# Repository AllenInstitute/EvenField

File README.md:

# EvenField - An easy, cost effective alternative to commercial based illumination systems for fluorescence microscopy

Coherent laser sources with Gaussian output profiles have been a preferred choice in many optical microscopy systems due to their high spatial intensity and monochromaticity. While these traits can beneficial in many applications, the high spatial coherence of these lasers results in interference effects as the light propagates through various optics toward the sample plane. These inference patterns superimposed onto the Gaussian laser profile result in an uneven illumination of the sample that get transferred into resulting images. For applications such as single molecule fluorescence imaging, the resulting field inhomogeneity  often clouds the signal that is to be detected. In addition, when these sources are used for imaging large areas that require tiling of multiple fields of view, the circular 2D illumination profile excites a larger field of view than is captured by the camera resulting in additional, unneeded photobleaching of these areas.

A simple deployment of a square multimode fiber between the illumination source and destination corrects this issue; however, the propogation of multiple laser modes through the fiber increases the potential for interference and results in additional laser speckle noise in the output beam. Researchers have developed several solutions to circumvent the laser speckle problem including, fiber vibration, tunable oscillating lenses, and spinning diffusers. 

We test some of these solutions and compare them to a commercial product, the Borealis system by Andor. 

----

Our full evaluation of this system can be found in our preprint : 
https://www.biorxiv.org/content/10.1101/2021.04.20.440683v1
  
---
  
We converged on a simple, cost-effective solution which we call the EvenField Illumination system. 

## So you're interested in building the EvenField system? ...We've got you covered.

This repository contains all of the information you will need to get started on building and employing the Evenfield system in your lab. This system can be used on a traditional, commercial laser launch or can be combined with the open source [Nicolase 3500] diode combiner and fiber launch for a cost effective, total solution for your illumination needs.

#### Hardware:
A complete list of associated hardware can be found [here](/Hardware).

This folder contains everything needed to build the EvenField system, including: 

* A complete [bill of materials] (optics and mounts)
* CAD renderings and .STEP files for the spinning diffuser component
* Details on custom optical fiber from Mitsubishi Cable Industries (MCI).
* Illuminator module for easy sensor size matching
* *Coming Soon:* Optical alignment guide 

#### Analysis:
The analysis code used for the EvenField publication has also been provided within this repo and may prove useful for evaluating the field flatness of your system. Code was written in Python and can be found [here].

[Nicolase 3500]: https://github.com/PRNicovich/NicoLase 
[bill of materials]: https://github.com/AllenInstitute/EvenField/blob/master/Hardware/EvenField%20Parts%20List.md
[here]: https://github.com/AllenInstitute/EvenField/tree/master/Analysis

#### Zoom illuminator update
Building on the published EvenField coupler and illuminator design, we implemented a microscope illuminator that features straightforward alignment and sensor-shape matching.  Illumination energy is delivered through an optical fiber - the details of which are not critical for use - and into a homogenizing prism.  The square exit face of this prism is imaged by a commercially-available zoom camera lens and a tube + objective lens pair to the sample plane.  Adjustments to the size and focus of the illumination field are straightfoward using the zoom and focus rings on the camera lens. On its own this assembly provides a simple and cheap square-field illumninator that will work with a wide range of detection camera formats.  Together with the EvenField homogenizer and NicoLase laser launch you can build your own microscopy illumination platform with custom laser power, color, and timing, evenly distributed over a field matching the detection camera FOV.  Add a chassis, cube, objective, and camera, and you've got a fluorescence microscope.

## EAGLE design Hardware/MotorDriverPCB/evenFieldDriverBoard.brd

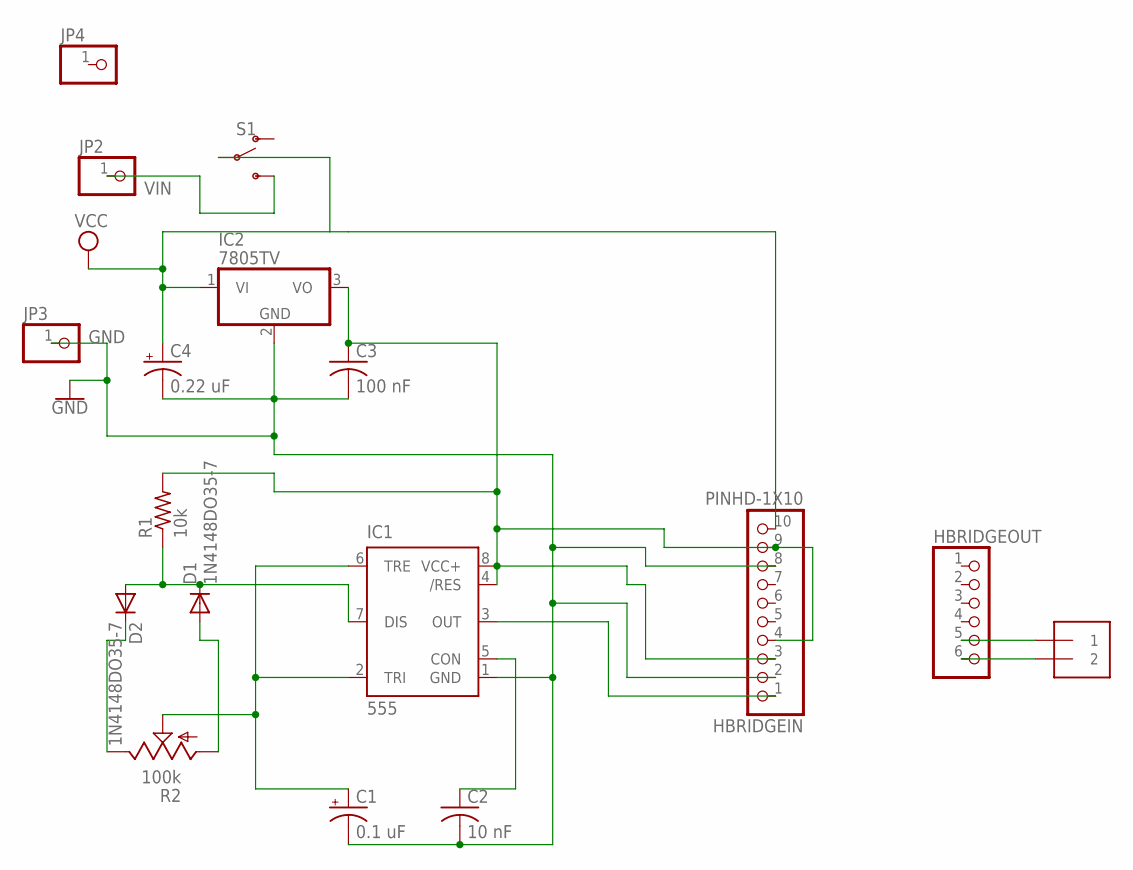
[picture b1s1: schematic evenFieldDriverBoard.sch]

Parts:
C1: 0.1 uF; B45181A
C2: 10 nF; C025-025X050
C3: 100 nF; C025-025X050
C4: 0.22 uF; B45181A
D1, D2: 1N4148DO35-7; DO35-7
HBRIDGEIN: PINHD-1X10; 1X10-BIG
HBRIDGEOUT: PINHD-1X6; 1X06
IC1: 555; DIP08
IC2: 7805TV; TO220V
J1: 1X2-3.5MM
JP2, JP3, JP4: PINHD-1X1; 1X01
R1: 10k; 0309V
R2: 100k; RJ9W
S1: SWITCH-SPDT-PTH-11.6X4.0MM; SWITCH_SPDT_PTH_11.6X4.0MM

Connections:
GND: C1.-, C2.2, C3.2, C4.-, HBRIDGEIN.2, HBRIDGEIN.8, IC1.1 (GND), IC2.2 (GND), JP3.1
unnamed: C3.1, HBRIDGEIN.3, HBRIDGEIN.4, HBRIDGEIN.9, IC1.4 (/RES), IC1.8 (VCC+), IC2.3 (VO), R1.2
unnamed: D2.C, R2.E
unnamed: D1.A, R2.A
unnamed: C1.+, IC1.2 (TRI), IC1.6 (TRE), R2.S
unnamed: C2.1, IC1.5 (CON)
unnamed: D1.C, D2.A, IC1.7 (DIS), R1.1
unnamed: HBRIDGEIN.1, IC1.3 (OUT)
unnamed: HBRIDGEOUT.5, J1.1
unnamed: HBRIDGEOUT.6, J1.2
VCC: C4.+, HBRIDGEIN.10, IC2.1 (VI), S1.2
VIN: JP2.1, S1.3 (S)

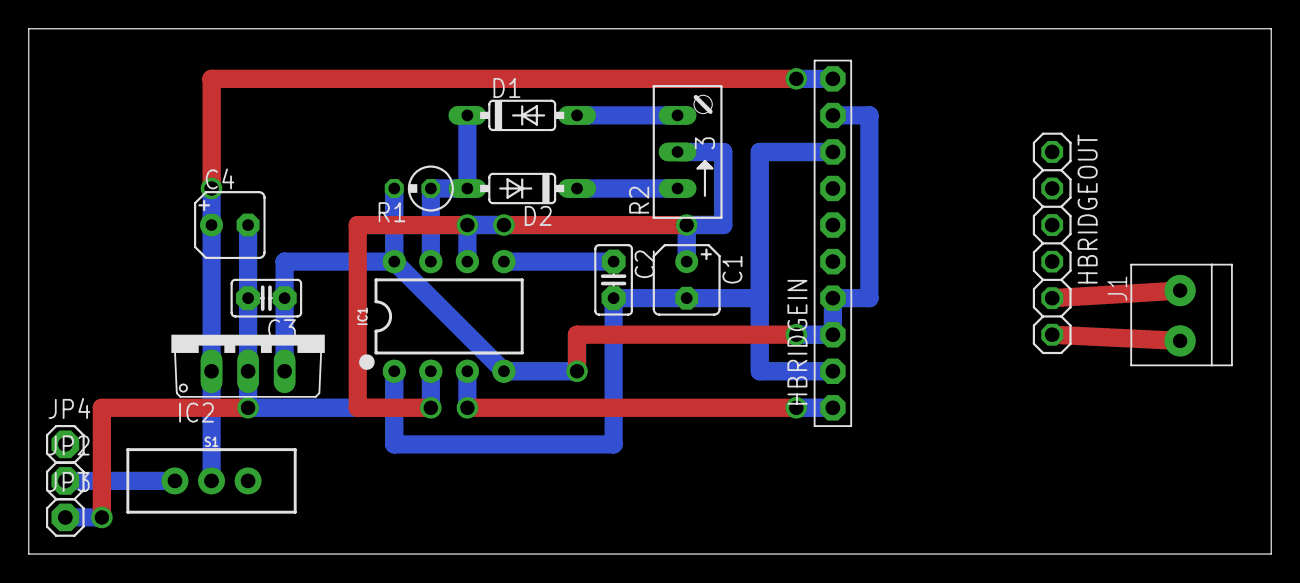
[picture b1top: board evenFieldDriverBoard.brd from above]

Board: 2 copper layers, 86.3 x 36.5 mm, 17 parts (0 on the bottom side), 12 nets.

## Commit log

2019-12-11 Create EvenField Parts List
2019-12-12 Create MCI Custom Fiber Design
2019-12-12 Update EvenField Parts List
2019-12-17 Upload code
2019-12-17 Upload EvenField CAD
2019-12-17 Fixed CAD import issues to SolidWorks
2019-12-18 Update README.md
    Edited readme to check for accuracy and word choice.
2020-01-02 Change CAD to .STEP
2020-01-02 1) Add analysis output .JSON files for manuscript data 2) Add CAD of EvenField system with NicoLase 3500 diode laser combiner
2020-02-05 Update with details on MCI fiber.
2020-02-05 Added P/N for MCI fiber
2020-03-09 Adding in motor driver PCB files.
2020-03-09 Added build notes and BOM for motor driver board.
2020-03-09 Update PCB build notes.
2020-07-17 Update LineProfileFigure and lineProfileResults.json to include ISO and speckle contrast results.
2022-06-17 Adding in info for the zoom illuminator.

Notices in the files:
parts and their libraries:
SparkFun-IC-Special-Function: Licensing: Creative Commons ShareAlike 4.0 International - https://creativecommons.org/licenses/by-sa/4.0
